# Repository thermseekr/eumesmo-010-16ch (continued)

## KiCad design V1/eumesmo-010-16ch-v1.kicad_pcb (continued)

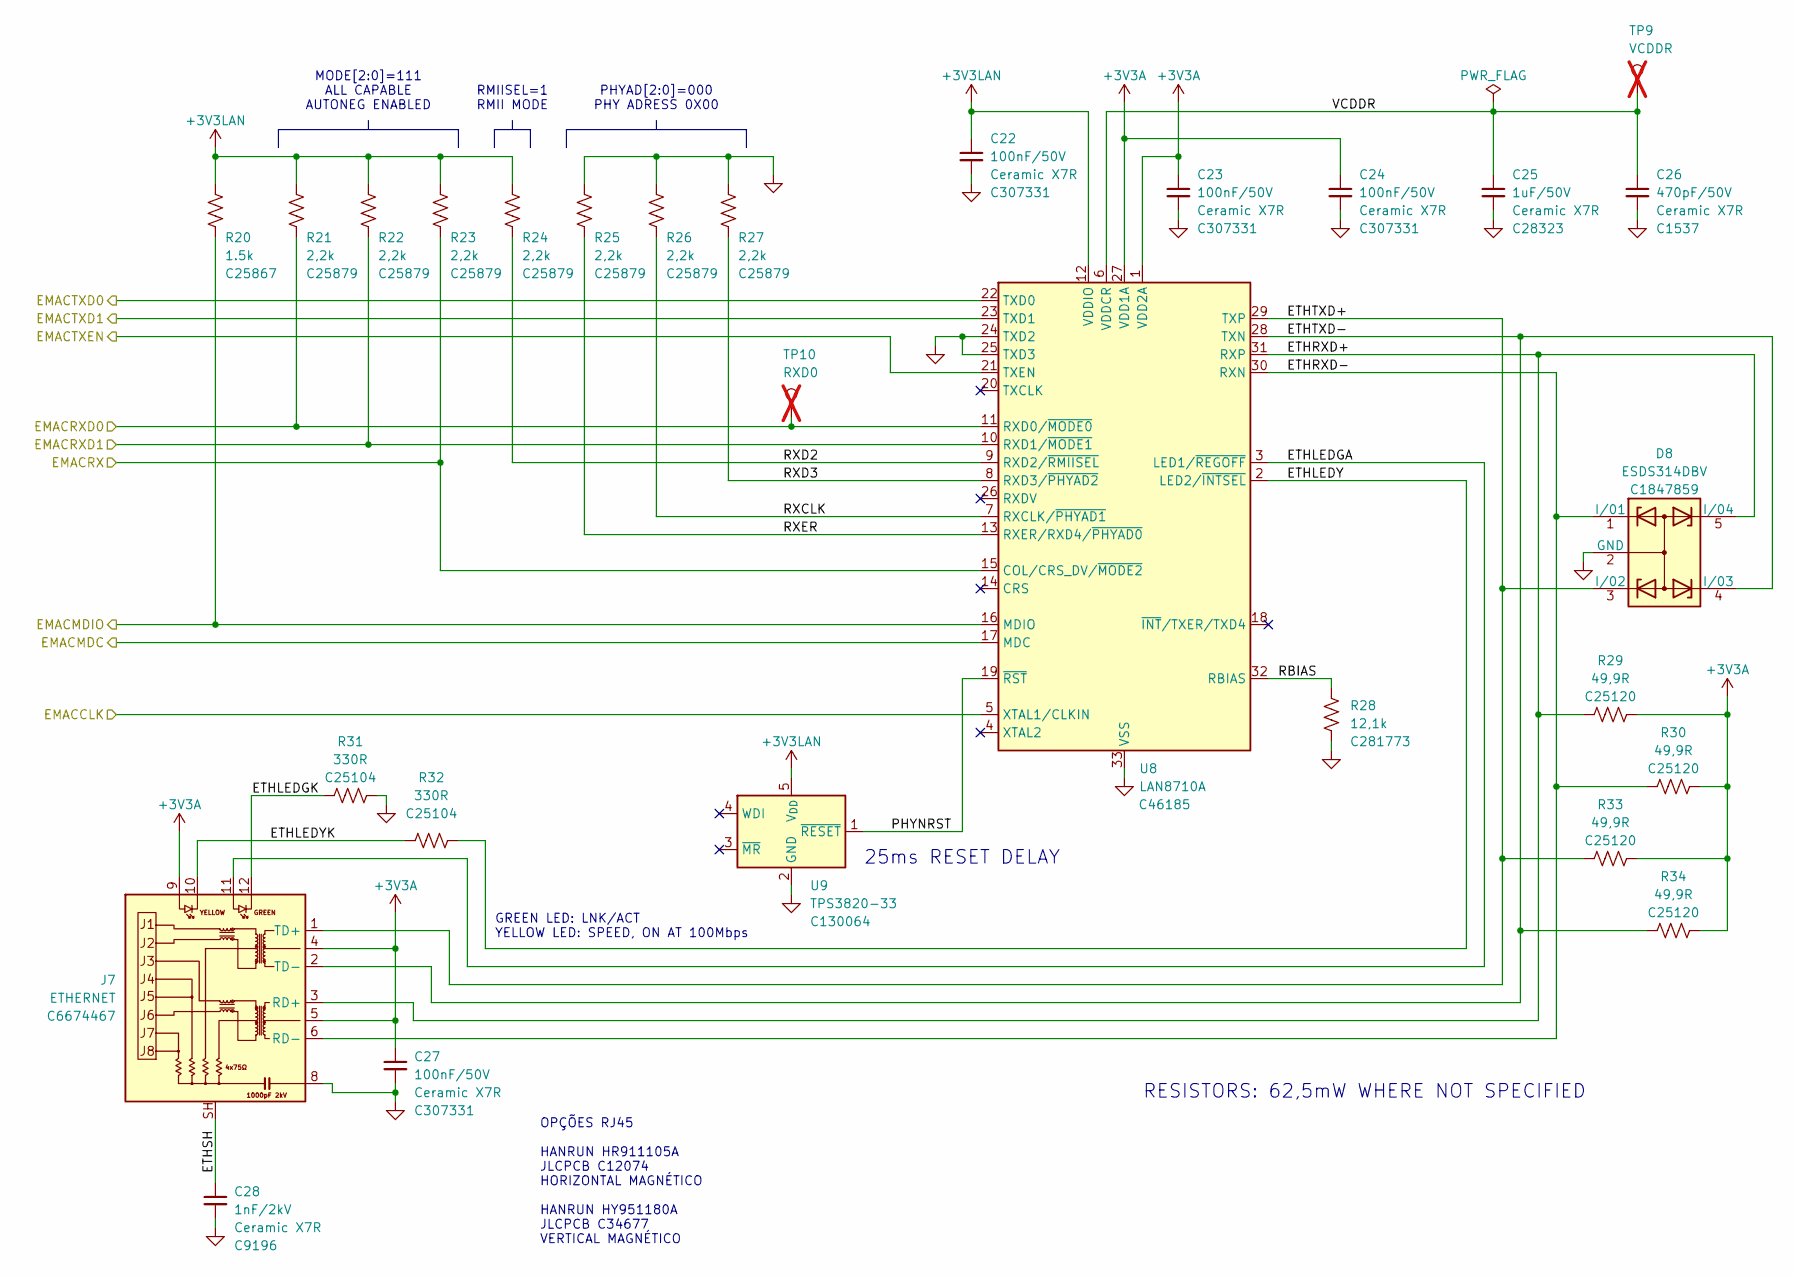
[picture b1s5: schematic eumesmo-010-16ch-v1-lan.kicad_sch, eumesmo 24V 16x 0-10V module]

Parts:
C22, C23, C24, C27: 100nF/50V; C_0402_1005Metric; Mfr PN CL05B104KB54PNC; LCSC Part # C307331
C25: 1uF/50V; C_0805_2012Metric; Mfr PN CL21B105KBFNNNE; LCSC Part # C28323
C26: 470pF/50V; C_0402_1005Metric; Mfr PN 0402B471K500NT; LCSC Part # C1537
C28: 1nF/2kV; C_1206_3216Metric; Mfr PN 1206B102K202NT; LCSC Part # C9196
D8: ESDS314DBV; SOT-23-5; Mfr PN ESDS314DBVR; LCSC Part # C1847859
J7: ETHERNET; RJ45_HanRun_HR915340A; Mfr PN HR915340AE; LCSC Part # C6674467
R20: 1.5k; R_0402_1005Metric; Mfr PN 0402WGF1501TCE; LCSC Part # C25867
R21, R22, R23, R24, R25, R26, R27: 2,2k; R_0402_1005Metric; Mfr PN 0402WGF2201TCE; LCSC Part # C25879
R28: 12,1k; R_0402_1005Metric; Mfr PN RT0402BRD0712K1L; LCSC Part # C281773
R29, R30, R33, R34: 49,9R; R_0402_1005Metric; Mfr PN 0402WGF499JTCE; LCSC Part # C25120
R31, R32: 330R; R_0402_1005Metric; Mfr PN 0402WGF3300TCE; LCSC Part # C25104
TP9: VCDDR; TestPoint_Pad_D1.5mm; not fitted
TP10: RXD0; TestPoint_Pad_D1.5mm; not fitted
U8: LAN8710A; QFN-32-1EP_5x5mm_P0.5mm_EP3.3x3.3mm_ThermalVias; Mfr PN LAN8710A-EZC-TR; LCSC Part # C46185
U9: TPS3820-33; SOT-23-5; Mfr PN TPS3820-33DBVR; LCSC Part # C130064

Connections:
+3V3A: C23.1, C24.1, C27.1, J7.4, J7.5, J7.9, R29.2, R30.2, R33.2, R34.2, U8.1 (VDD2A), U8.27 (VDD1A); also elsewhere on the board
+3V3LAN: C22.1, R20.1, R21.1, R22.1, R23.1, R24.1, U8.12 (VDDIO), U9.5 (V_{DD}); also elsewhere on the board
/LAN/EMACCLK: U8.5 (XTAL1/CLKIN); also elsewhere on the board
/LAN/EMACMDC: U8.17 (MDC); also elsewhere on the board
/LAN/EMACMDIO: R20.2, U8.16 (MDIO); also elsewhere on the board
/LAN/EMACRX: R23.2, U8.15 (COL/CRS_DV/~MODE2); also elsewhere on the board
/LAN/EMACRXD0: R21.2, TP10.1, U8.11 (RXD0/~MODE0); also elsewhere on the board
/LAN/EMACRXD1: R22.2, U8.10 (RXD1/~MODE1); also elsewhere on the board
/LAN/EMACTXD0: U8.22 (TXD0); also elsewhere on the board
/LAN/EMACTXD1: U8.23 (TXD1); also elsewhere on the board
/LAN/EMACTXEN: U8.21 (TXEN); also elsewhere on the board
/LAN/ETHLEDGA: J7.11, U8.3 (LED1/~REGOFF)
/LAN/ETHLEDGK: J7.12, R31.1
/LAN/ETHLEDY: R32.2, U8.2 (LED2/~INTSEL)
/LAN/ETHLEDYK: J7.10, R32.1
/LAN/ETHRXD+: D8.5 (I/04), J7.3 (RD+), R29.1, U8.31 (RXP)
/LAN/ETHRXD-: D8.1 (I/01), J7.6 (RD-), R30.1, U8.30 (RXN)
/LAN/ETHSH: C28.1, J7.SH
/LAN/ETHTXD+: D8.3 (I/02), J7.1 (TD+), R33.1, U8.29 (TXP)
/LAN/ETHTXD-: D8.4 (I/03), J7.2 (TD-), R34.1, U8.28 (TXN)
/LAN/PHYNRST: U8.19 (~RST), U9.1 (~RESET)
/LAN/RBIAS: R28.1, U8.32 (RBIAS)
/LAN/RXCLK: R26.2, U8.7 (RXCLK/~PHYAD1)
/LAN/RXD2: R24.2, U8.9 (RXD2/~RMIISEL)
/LAN/RXD3: R27.2, U8.8 (RXD3/~PHYAD2)
/LAN/RXER: R25.2, U8.13 (RXER/RXD4/~PHYAD0)
/LAN/VCDDR: C25.1, C26.1, U8.6 (VDDCR)
GND: C22.2, C23.2, C24.2, C25.2, C26.2, C27.2, C28.2, D8.2 (GND), J7.8, R25.1, R26.1, R27.1, R28.2, R31.2, U8.24 (TXD2), U8.25 (TXD3), U8.33 (VSS), U9.2 (GND); also elsewhere on the board

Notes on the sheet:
25ms RESET DELAY
OPÇÕES RJ45 HANRUN HR911105A JLCPCB C12074 HORIZONTAL MAGNÉTICO HANRUN HY951180A JLCPCB C34677 VERTICAL MAGNÉTICO
GREEN LED: LNK/ACT YELLOW LED: SPEED, ON AT 100Mbps
MODE[2:0]=111 ALL CAPABLE AUTONEG ENABLED
PHYAD[2:0]=000 PHY ADRESS 0X00
RMIISEL=1 RMII MODE
RESISTORS: 62,5mW WHERE NOT SPECIFIED

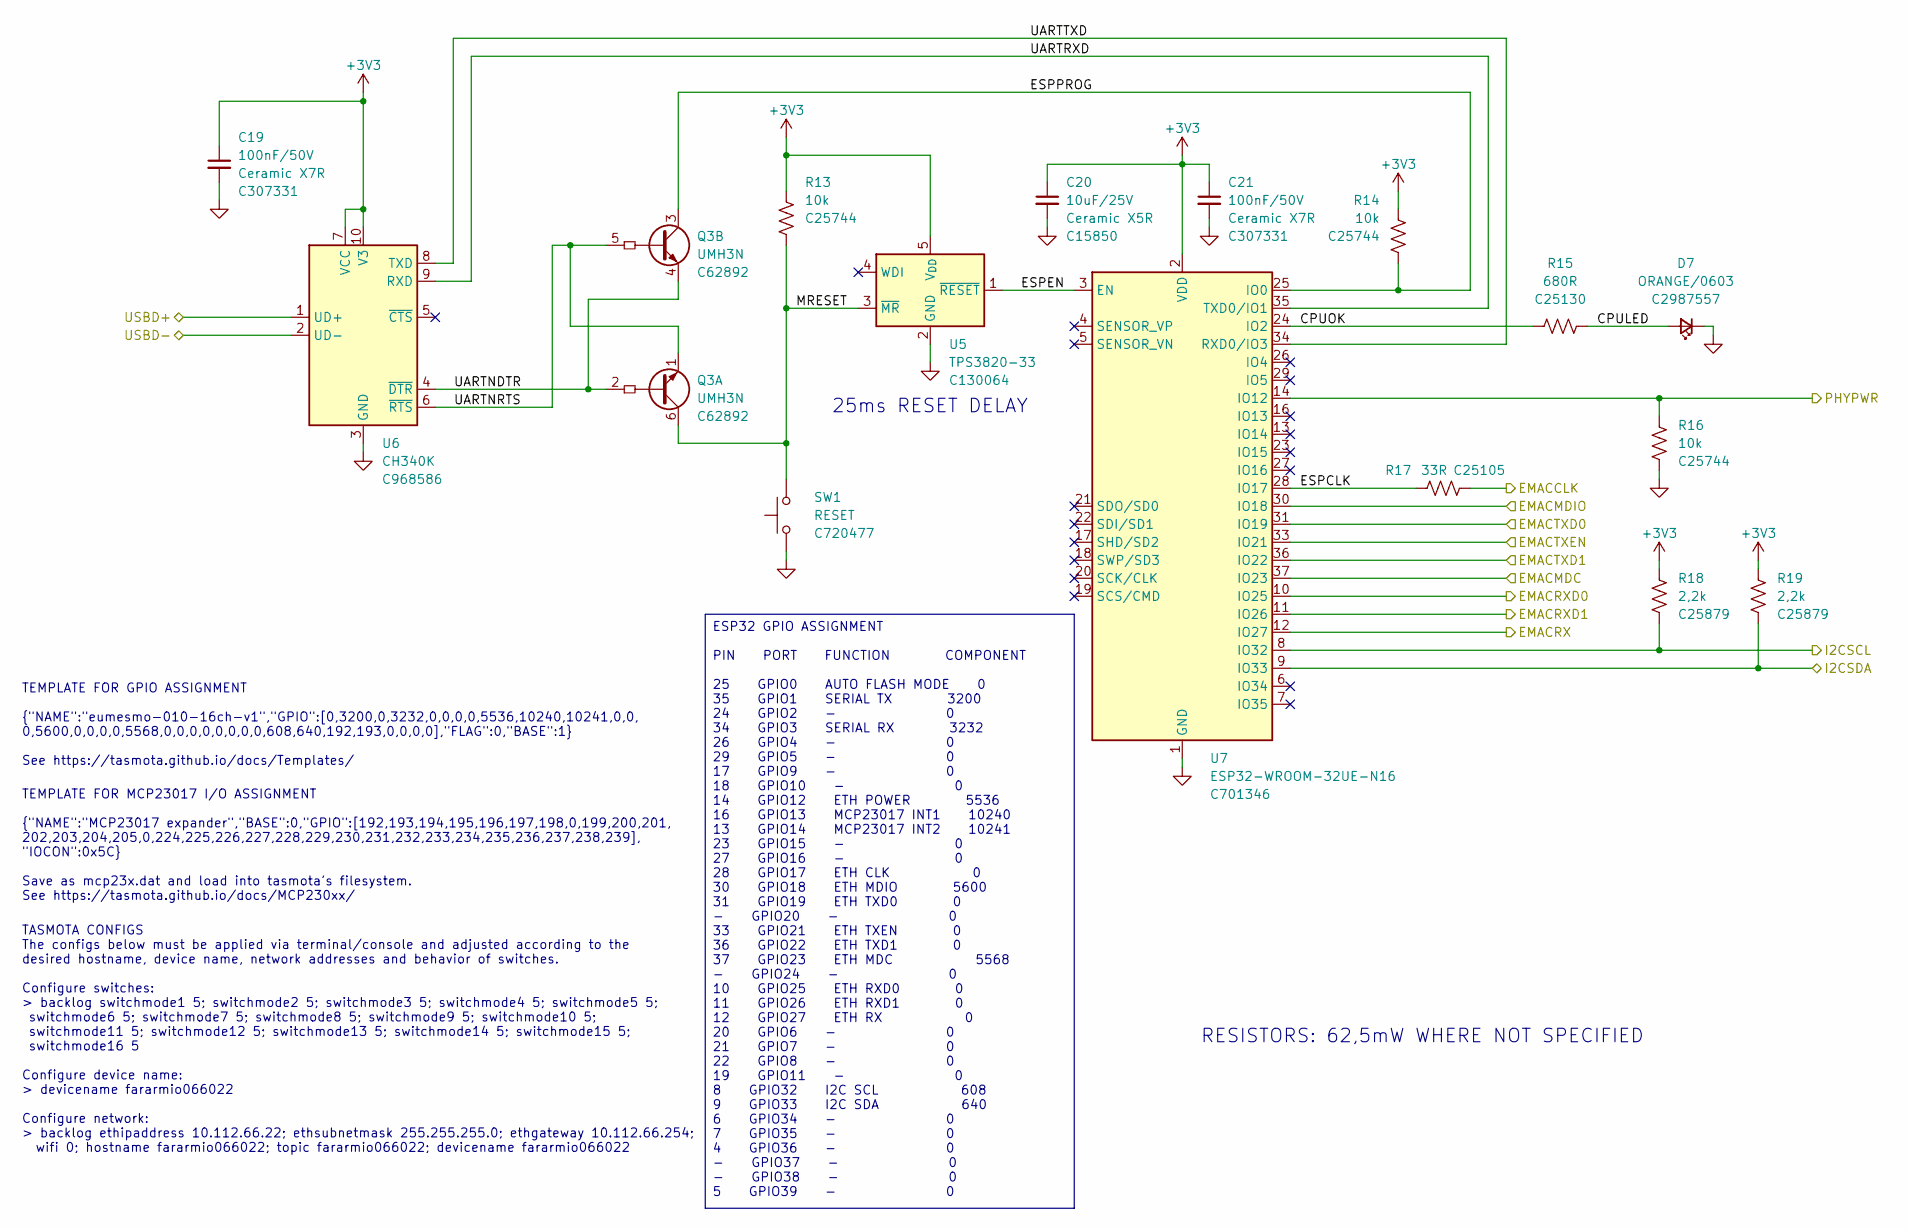
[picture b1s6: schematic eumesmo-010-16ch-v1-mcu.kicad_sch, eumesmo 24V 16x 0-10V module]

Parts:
C19, C21: 100nF/50V; C_0402_1005Metric; Mfr PN CL05B104KB54PNC; LCSC Part # C307331
C20: 10uF/25V; C_0805_2012Metric; Mfr PN CL21A106KAYNNNE; LCSC Part # C15850
D7: ORANGE/0603; LED_0603_1608Metric; Mfr PN 19-217/S2C-AL1M2VY/6T; LCSC Part # C2987557
Q3: UMH3N; SOT-363_SC-70-6; Mfr PN UMH3N; LCSC Part # C62892
R13, R14, R16: 10k; R_0402_1005Metric; Mfr PN 0402WGF1002TCE; LCSC Part # C25744
R15: 680R; R_0402_1005Metric; Mfr PN 0402WGF6800TCE; LCSC Part # C25130
R17: 33R; R_0402_1005Metric; Mfr PN 0402WGF330JTCE; LCSC Part # C25105
R18, R19: 2,2k; R_0402_1005Metric; Mfr PN 0402WGF2201TCE; LCSC Part # C25879
SW1: RESET; SW_SPST_Xunpu_TS1088AR02016; Mfr PN TS-1088-AR02016; LCSC Part # C720477
U5: TPS3820-33; SOT-23-5; Mfr PN TPS3820-33DBVR; LCSC Part # C130064
U6: CH340K; SSOP-10-1EP_3.9x4.9mm_P1mm_EP2.1x3.3mm; Mfr PN CH340K; LCSC Part # C968586
U7: ESP32-WROOM-32UE-N16; ESP32-WROOM-32U; Mfr PN ESP32-WROOM-32UE-N16; LCSC Part # C701346

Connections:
+3V3: C19.1, C20.1, C21.1, R13.1, R14.1, R18.1, R19.1, U5.5 (V_{DD}), U6.7 (VCC), U6.10 (V3), U7.2 (VDD); also elsewhere on the board
/I2C Devices/I2CSCL: R18.2, U7.8 (IO32); also elsewhere on the board
/I2C Devices/I2CSDA: R19.2, U7.9 (IO33); also elsewhere on the board
/LAN/EMACCLK: R17.2; also elsewhere on the board
/LAN/EMACMDC: U7.37 (IO23); also elsewhere on the board
/LAN/EMACMDIO: U7.30 (IO18); also elsewhere on the board
/LAN/EMACRX: U7.12 (IO27); also elsewhere on the board
/LAN/EMACRXD0: U7.10 (IO25); also elsewhere on the board
/LAN/EMACRXD1: U7.11 (IO26); also elsewhere on the board
/LAN/EMACTXD0: U7.31 (IO19); also elsewhere on the board
/LAN/EMACTXD1: U7.36 (IO22); also elsewhere on the board
/LAN/EMACTXEN: U7.33 (IO21); also elsewhere on the board
/MCU/CPULED: D7.2 (A), R15.2
/MCU/CPUOK: R15.1, U7.24 (IO2)
/MCU/ESPCLK: R17.1, U7.28 (IO17)
/MCU/ESPEN: U5.1 (~RESET), U7.3 (EN)
/MCU/ESPPROG: Q3.3 (C2), R14.2, U7.25 (IO0)
/MCU/MRESET: Q3.6 (C1), R13.2, SW1.2, U5.3 (~MR)
/MCU/PHYPWR: R16.1, U7.14 (IO12); also elsewhere on the board
/MCU/UARTNDTR: Q3.2 (B1), Q3.4 (E2), U6.4 (~DTR)
/MCU/UARTNRTS: Q3.1 (E1), Q3.5 (B2), U6.6 (~RTS)
/MCU/UARTRXD: U6.9 (RXD), U7.35 (TXD0/IO1)
/MCU/UARTTXD: U6.8 (TXD), U7.34 (RXD0/IO3)
/MCU/USBD+: U6.1 (UD+); also elsewhere on the board
/MCU/USBD-: U6.2 (UD-); also elsewhere on the board
GND: C19.2, C20.2, C21.2, D7.1 (K), R16.2, SW1.1, U5.2 (GND), U6.3 (GND), U6.11 (GND), U7.1 (GND), U7.15 (GND), U7.38 (GND), U7.39 (GND); also elsewhere on the board

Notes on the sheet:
TASMOTA CONFIGS The configs below must be applied via terminal/console and adjusted according to the desired hostname, device name, network addresses and behavior of switches. Configure switches: > backlog switchmode1 5; switchmode2 5; switchmode3 5; switchmode4 5; switchmode5 5; switchmode6 5; swi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
25ms RESET DELAY
TEMPLATE FOR GPIO ASSIGNMENT {"NAME":"eumesmo-010-16ch-v1","GPIO":[0,3200,0,3232,0,0,0,0,5536,10240,10241,0,0, 0,5600,0,0,0,0,5568,0,0,0,0,0,0,0,0,608,640,192,193,0,0,0,0],"FLAG":0,"BASE":1} See https://tasmota.github.io/docs/Templates/
TEMPLATE FOR MCP23017 I/O ASSIGNMENT {"NAME":"MCP23017 expander","BASE":0,"GPIO":[192,193,194,195,196,197,198,0,199,200,201, 202,203,204,205,0,224,225,226,227,228,229,230,231,232,233,234,235,236,237,238,239], "IOCON":0x5C} Save as mcp23x.dat and load into tasmota's filesystem. See https://tasmota.g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
RESISTORS: 62,5mW WHERE NOT SPECIFIED
ESP32 GPIO ASSIGNMENT PIN PORT FUNCTION COMPONENT 25 GPIO0 AUTO FLASH MODE 0 35 GPIO1 SERIAL TX 3200 24 GPIO2 - 0 34 GPIO3 SERIAL RX 3232 26 GPIO4 - 0 29 GPIO5 - 0 17 GPIO9 - 0 18 GPIO10 - 0 14 GPIO12 ETH POWER 5536 16 GPIO13 MCP23017 INT1 10240 13 GPIO14 MCP23017 INT2 10241 23 GPIO15 - 0 27 GPIO16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

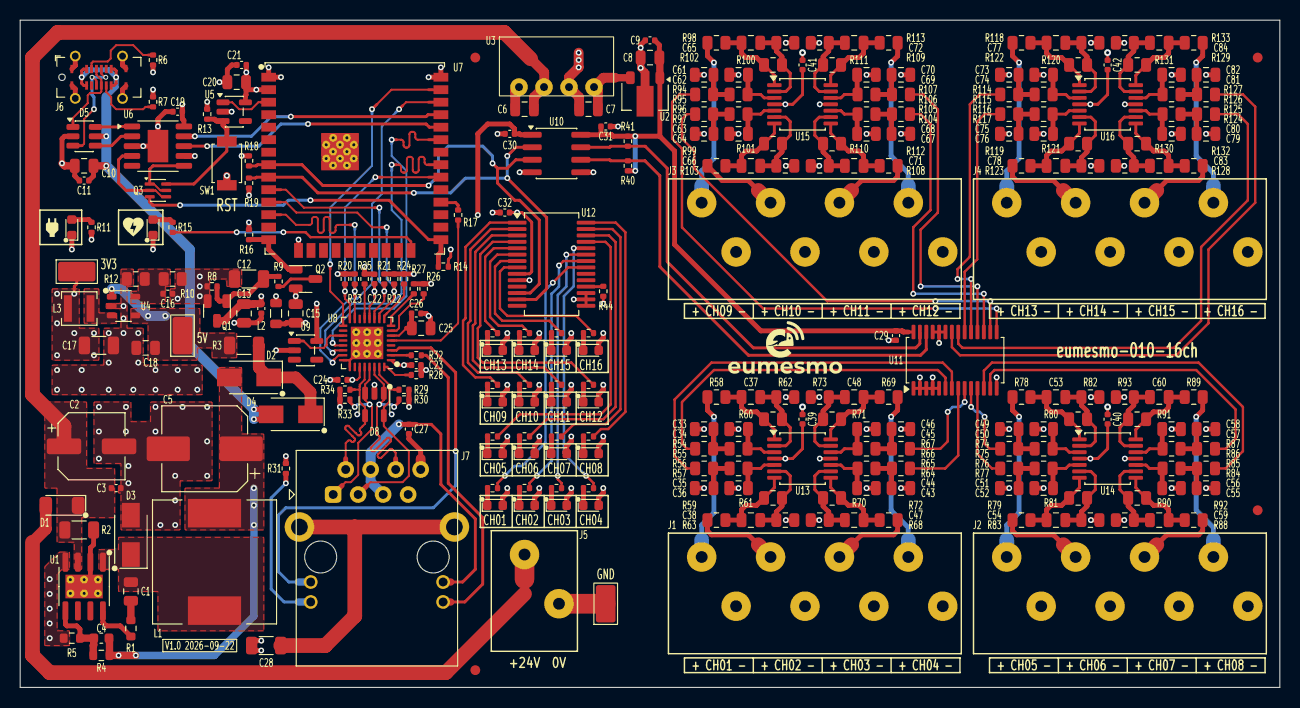
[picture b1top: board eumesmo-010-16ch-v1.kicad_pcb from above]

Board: 4 copper layers, 128.0 x 67.8 mm, 278 parts (0 on the bottom side), 198 nets.

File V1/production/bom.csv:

Designator,Footprint,Quantity,Value,LCSC Part #
"C1, C33, C34, C35, C36, C43, C44, C45, C46, C49, C50, C51, C52, C55, C56, C57, C58, C61, C62, C63, C64, C67, C68, C69, C70, C73, C74, C75, C76, C79, C80, C81, C82",0805,33,100nF/100V,C28233
"C10, C13, C15, C18, C20, C7",0805,6,10uF/25V,C15850
"C11, C14, C19, C21, C22, C23, C24, C27, C29, C3, C30, C31, C32, C39, C40, C41, C42, C9",0402,18,100nF/50V,C307331
"C12, C17",1206,2,22uF/10V,C5672
C16,0402,1,22pF/50V,C1555
C2,CP_Elec_6.3x5.4,1,47uF/35V,C129415
"C25, C6, C8",0805,3,1uF/50V,C28323
C26,0402,1,470pF/50V,C1537
C28,1206,1,1nF/2kV,C9196
"C37, C38, C47, C48, C53, C54, C59, C60, C65, C66, C71, C72, C77, C78, C83, C84",0805,16,100pF/50V,C1790
C4,0603,1,12pF/50V,C38523
C5,CP_Elec_8x10.5,1,470uF/16V,C96179
D1,D_SOD-123,1,SM4007PL,C64898
"D10, D11, D12, D13, D14, D15, D16, D17, D18, D19, D20, D21, D22, D23, D24, D6, D7, D9",0603,18,ORANGE/0603,C2987557
"D2, D4",D_SMA,2,SS34,C8678
D3,D_SMA,1,SS510,C65010
D5,SOT-23-6,1,USBLC6-2SC6,C7519
D8,SOT-23-5,1,ESDS314DBV,C1847859
"J1, J2, J3, J4",TerminalBlock_Wago_250-208_1x08_P3.5mm_45Degree,4,250-208,C2833587
J5,TerminalBlock_Wago_250-202_1x02_P3.5mm_45Degree,1,250-202,C2765061
J6,USB_C_Receptacle_ShouHan_TYPE-C-16PLT-H10.0,1,USB_C_Receptacle_USB2.0,C3151749
J7,RJ45_HanRun_HR915340A,1,ETHERNET,C6674467
L1,L_12x12mm_H6mm,1,"33uH 2,1A",C169386
L2,0805,1,2A 600R,C139168
L3,L_3x3mm_H1.5mm,1,"2,2uH 1,5A",C370424
Q1,SOT-23,1,WPM2015-3/TR,C558305
Q2,SOT-23,1,MMUN2211LT3G,C150229
Q3,SOT-363_SC-70-6,1,UMH3N,C62892
R1,0603,1,"5,1R/100mW",C25197
R10,0805,1,100k/125mW,C149504
"R100, R101, R110, R111, R120, R121, R130, R131, R60, R61, R70, R71, R80, R81, R90, R91",0805,16,11k/125mW,C17429
"R102, R103, R104, R105, R106, R107, R112, R113, R114, R115, R116, R117, R122, R123, R124, R125, R126, R127, R132, R133, R54, R55, R56, R57, R62, R63, R64, R65, R66, R67, R72, R73, R74, R75, R76, R77, R82, R83, R84, R85, R86, R87, R92, R93, R94, R95, R96, R97",0805,48,10k/125mW,C17414
"R108, R109, R118, R119, R128, R129, R58, R59, R68, R69, R78, R79, R88, R89, R98, R99",0805,16,47R/125mW,C17714
"R11, R15, R35, R36, R37, R38, R39, R42, R43, R45, R46, R47, R48, R49, R50, R51, R52, R53",0402,18,680R,C25130
R12,0805,1,"22,1k/125mW",C17552
"R13, R14, R16, R8",0402,4,10k,C25744
R17,0402,1,33R,C25105
"R18, R19, R21, R22, R23, R24, R25, R26, R27, R40, R41",0402,11,"2,2k",C25879
R2,1206,1,30mR/333mW,C473665
R20,0402,1,1.5k,C25867
R28,0402,1,"12,1k",C281773
"R29, R30, R33, R34",0402,4,"49,9R",C25120
R3,1206,1,"0,1R",C309528
"R31, R32",0402,2,330R,C25104
R4,0603,1,300k/100mW,C23024
"R44, R9",0402,2,1k,C11702
R5,0603,1,"52,3k/100mW",C23198
"R6, R7",0402,2,"5,1k",C105872
SW1,SW_SPST_Xunpu_TS1088AR02016,1,RESET,C720477
"TP2, TP3, TP8",TestPoint_Keystone_5019_Miniature,3,TP5019,C238131
U1,SOIC-8-1EP_3.9x4.9mm_P1.27mm_EP2.41x3.81mm_ThermalVias,1,TX4138,C329267
U10,SOIC-8_3.9x4.9mm_P1.27mm,1,ISO1540,C179739
U11,TSSOP-28_4.4x9.7mm_P0.65mm,1,PCA9685PW,C2678753
U12,SSOP-28_5.3x10.2mm_P0.65mm,1,MCP23017,C506653
"U13, U14, U15, U16",TSSOP-14_4.4x5mm_P0.65mm,4,TLV274,C9914
U2,SOT-89-3,1,L78L05_SOT89,C42738
U3,Ylptec BxxxxS-1WR3,1,B2412S-1WR3,C5369469
U4,SOT-23-5_Shorter_Pins,1,SY8089A1AAC,C479074
"U5, U9",SOT-23-5,2,TPS3820-33,C130064
U6,SSOP-10-1EP_3.9x4.9mm_P1mm_EP2.1x3.3mm,1,CH340K,C968586
U7,ESP32-WROOM-32U,1,ESP32-WROOM-32UE-N16,C701346
U8,QFN-32-1EP_5x5mm_P0.5mm_EP3.3x3.3mm_ThermalVias,1,LAN8710A,C46185

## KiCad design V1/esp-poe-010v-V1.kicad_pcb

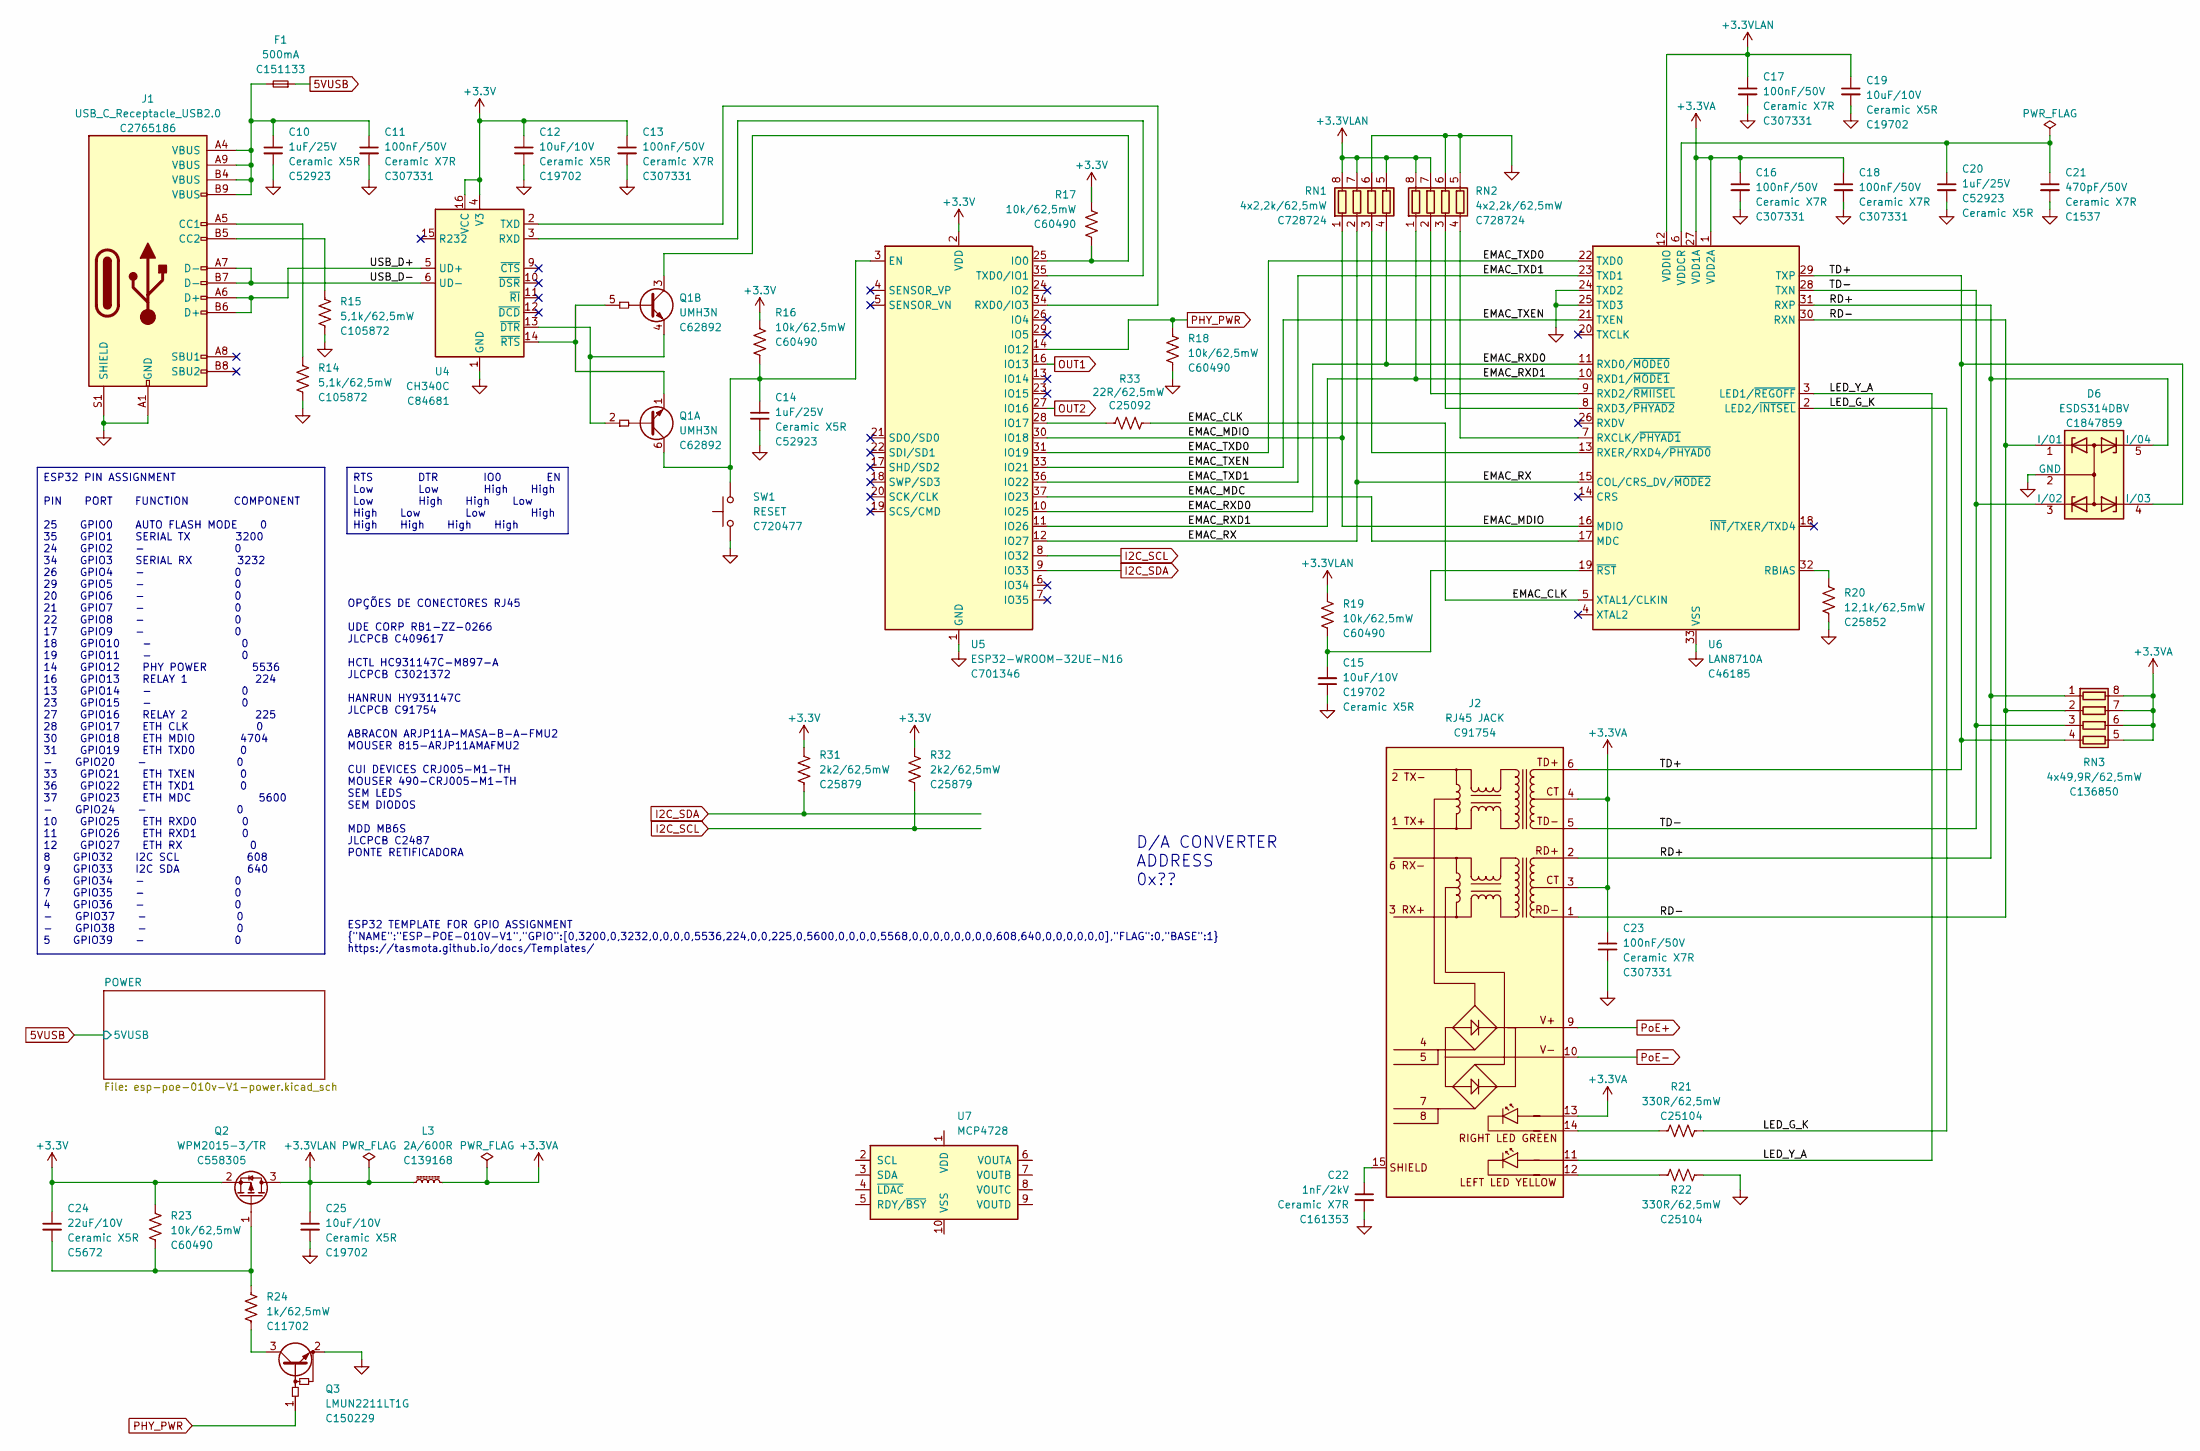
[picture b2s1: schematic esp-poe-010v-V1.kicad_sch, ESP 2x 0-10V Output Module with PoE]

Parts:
C10, C14, C20: 1uF/25V; C_0402_1005Metric; Mfr PN CL05A105KA5NQNC; JLCPCB BOM 1
C11, C13, C16, C17, C18, C23: 100nF/50V; C_0402_1005Metric; Mfr PN CL05B104KB54PNC; JLCPCB BOM 1
C12: 10uF/10V; C_0603_1608Metric; Mfr PN CL10A106KP8NNNC; LCSC Part # C19702
C15, C19, C25: 10uF/10V; C_0603_1608Metric; Mfr PN CL10A106KP8NNNC; JLCPCB BOM 1
C21: 470pF/50V; C_0402_1005Metric; Mfr PN 0402B471K500NT; JLCPCB BOM 1
C22: 1nF/2kV; C_1206_3216Metric; Mfr PN GR431BR7LA102KW66L; JLCPCB BOM 1
C24: 22uF/10V; C_1206_3216Metric; Mfr PN CL31A226KPHNNNE; JLCPCB BOM 1
D6: ESDS314DBV; SOT-23-5; Mfr PN ESDS314DBVR; JLCPCB BOM 1
F1: 500mA; Fuse_1206_3216Metric; Mfr PN 0466.500NRHF; JLCPCB BOM 1
J1: USB_C_Receptacle_USB2.0; USB_C_Receptacle_GCT_USB4105-xx-A_16P_TopMnt_Horizontal; Mfr PN TYPE-C 16PIN 2MD(073); JLCPCB BOM 1
J2: RJ45 JACK; RJ45_HanRun_HY931147C; Mfr PN HY931147C; JLCPCB BOM 1
L3: 2A/600R; L_0805_2012Metric; Mfr PN CBM201209U601T; JLCPCB BOM 1
Q1: UMH3N; SOT-363_SC-70-6; Mfr PN UMH3N; JLCPCB BOM 1
Q2: WPM2015-3/TR; SOT-23; Mfr PN WPM2015-3/TR; JLCPCB BOM 1
Q3: LMUN2211LT1G; SOT-23; Mfr PN MMUN2211LT3G; LCSC Part # C150229
R14, R15: 5,1k/62,5mW; R_0402_1005Metric; Mfr PN RC0402FR-075K1L; JLCPCB BOM 1
R16, R17, R18, R19, R23: 10k/62,5mW; R_0402_1005Metric; Mfr PN RC0402FR-0710KL; LCSC Part # C60490
R20: 12,1k/62,5mW; R_0402_1005Metric; Mfr PN 0402WGF1212TCE; JLCPCB BOM 1
R21, R22: 330R/62,5mW; R_0402_1005Metric; Mfr PN 0402WGF3300TCE; LCSC Part # C25104
R24: 1k/62,5mW; R_0402_1005Metric; Mfr PN 0402WGF1001TCE; LCSC Part # C11702
R31, R32: 2k2/62,5mW; R_0402_1005Metric; Mfr PN 0402WGF2201TCE; LCSC Part # C25879
R33: 22R/62,5mW; R_0402_1005Metric; Mfr PN 0402WGF220JTCE; JLCPCB BOM 1
RN1, RN2: 4x2,2k/62,5mW; R_Array_Convex_4x0402; Mfr PN YC124-FR-072K2L; JLCPCB BOM 1
RN3: 4x49,9R/62,5mW; R_Array_Convex_4x0402; Mfr PN YC124-FR-0749R9L; JLCPCB BOM 1
SW1: RESET; SW_SPST_Xunpu_TS1088AR02016; Mfr PN TS-1088-AR02016; JLCPCB BOM 1
U4: CH340C; SOIC-16_3.9x9.9mm_P1.27mm; Mfr PN CH340C; JLCPCB BOM 1
U5: ESP32-WROOM-32UE-N16; ESP32-WROOM-32U; Mfr PN ESP32-WROOM-32UE-N16; JLCPCB BOM 1
U6: LAN8710A; QFN-32-1EP_5x5mm_P0.5mm_EP3.3x3.3mm_ThermalVias; Mfr PN LAN8710A-EZC-TR; JLCPCB BOM 1
U7: MCP4728; MSOP-10_3x3mm_P0.5mm

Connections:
5VUSB: F1.1; also elsewhere on the board
+3.3V: C12.1, C13.1, C24.1, Q2.2 (S), R16.1, R17.1, R23.1, R31.1, R32.1, U4.4 (V3), U4.16 (VCC), U5.2 (VDD); also elsewhere on the board
+3.3VA: C16.1, C18.1, C23.1, J2.3 (CT), J2.4 (CT), J2.13 (RLED+), L3.2, RN3.5 (R4.2), RN3.6 (R3.2), RN3.7 (R2.2), RN3.8 (R1.2), U6.1 (VDD2A), U6.27 (VDD1A)
+3.3VLAN: C17.1, C19.1, C25.1, L3.1, Q2.3 (D), R19.2, RN1.5 (R4.2), RN1.7 (R2.2), RN1.8 (R1.2), RN2.7 (R2.2), RN2.8 (R1.2), U6.12 (VDDIO)
/EMAC_CLK: R33.2, U6.5 (XTAL1/CLKIN)
/EMAC_MDC: U5.37 (IO23), U6.17 (MDC)
/EMAC_MDIO: RN1.1 (R1.1), U5.30 (IO18), U6.16 (MDIO)
/EMAC_RX: RN1.2 (R2.1), U5.12 (IO27), U6.15 (COL/CRS_DV/~MODE2)
/EMAC_RXD0: RN1.4 (R4.1), U5.10 (IO25), U6.11 (RXD0/~MODE0)
/EMAC_RXD1: RN2.1 (R1.1), U5.11 (IO26), U6.10 (RXD1/~MODE1)
/EMAC_TXD0: U5.31 (IO19), U6.22 (TXD0)
/EMAC_TXD1: U5.36 (IO22), U6.23 (TXD1)
/EMAC_TXEN: U5.33 (IO21), U6.21 (TXEN)
/LED_G_K: R21.2, U6.2 (LED2/~INTSEL)
/LED_Y_A: J2.11 (LLED+), U6.3 (LED1/~REGOFF)
/RD+: D6.5 (I/04), J2.2 (RD+), RN3.1 (R1.1), U6.31 (RXP)
/RD-: D6.1 (I/01), J2.1 (RD-), RN3.2 (R2.1), U6.30 (RXN)
/TD+: D6.4 (I/03), J2.6 (TD+), RN3.4 (R4.1), U6.29 (TXP)
/TD-: D6.3 (I/02), J2.5 (TD-), RN3.3 (R3.1), U6.28 (TXN)
/USB_D+: J1.A6 (D+), J1.B6 (D+), U4.5 (UD+)
/USB_D-: J1.A7 (D-), J1.B7 (D-), U4.6 (UD-)
GND: C10.2, C11.2, C12.2, C13.2, C14.2, C15.1, C16.2, C17.2, C18.2, C19.2, C20.2, C21.2, C22.2, C23.2, C25.2, D6.2 (GND), J1.A1 (GND), J1.A12 (GND), J1.B1 (GND), J1.B12 (GND), J1.S1 (SHIELD), Q3.2 (E), R14.2, R15.2, R18.1, R20.2, R22.2, RN1.6 (R3.2), RN2.5 (R4.2), RN2.6 (R3.2), SW1.1, U4.1 (GND), U5.1 (GND), U5.15 (GND), U5.38 (GND), U5.39 (GND), U6.24 (TXD2), U6.25 (TXD3), U6.33 (VSS); also elsewhere on the board
I2C_SCL: R32.2, U5.8 (IO32)
I2C_SDA: R31.2, U5.9 (IO33)
unnamed: C10.1, C11.1, F1.2, J1.A4 (VBUS), J1.A9 (VBUS), J1.B4 (VBUS), J1.B9 (VBUS)
unnamed: J1.A5 (CC1), R14.1
unnamed: J1.B5 (CC2), R15.1
unnamed: J2.12 (LLED-), R22.1
unnamed: J2.14 (RLED-), R21.1
unnamed: C22.1, J2.15 (SHIELD)
unnamed: Q1.2 (B1), Q1.4 (E2), U4.13 (~DTR)
unnamed: C14.1, Q1.6 (C1), R16.2, SW1.2, U5.3 (EN)
unnamed: Q1.1 (E1), Q1.5 (B2), U4.14 (~RTS)
unnamed: Q1.3 (C2), R17.2, U5.25 (IO0)
unnamed: C24.2, Q2.1 (G), R23.2, R24.1
unnamed: Q3.3 (C), R24.2
unnamed: RN1.3 (R3.1), U6.13 (RXER/RXD4/~PHYAD0)
unnamed: RN2.2 (R2.1), U6.9 (RXD2/~RMIISEL)
unnamed: RN2.3 (R3.1), U6.8 (RXD3/~PHYAD2)
unnamed: RN2.4 (R4.1), U6.7 (RXCLK/~PHYAD1)
unnamed: U4.3 (RXD), U5.35 (TXD0/IO1)
unnamed: U4.2 (TXD), U5.34 (RXD0/IO3)
unnamed: R33.1, U5.28 (IO17)
unnamed: R20.1, U6.32 (RBIAS)
unnamed: C20.1, C21.1, U6.6 (VDDCR)
unnamed: C15.2, R19.1, U6.19 (~RST)
OUT1: U5.16 (IO13)
OUT2: U5.27 (IO16)
PHY_PWR: Q3.1 (B), R18.2, U5.14 (IO12)
PoE+: J2.9 (V+); also elsewhere on the board
PoE-: J2.10 (V-); also elsewhere on the board

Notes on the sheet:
D/A CONVERTER ADDRESS 0x??
OPÇÕES DE CONECTORES RJ45 UDE CORP RB1-ZZ-0266 JLCPCB C409617 HCTL HC931147C-M897-A JLCPCB C3021372 HANRUN HY931147C JLCPCB C91754 ABRACON ARJP11A-MASA-B-A-FMU2 MOUSER 815-ARJP11AMAFMU2 CUI DEVICES CRJ005-M1-TH MOUSER 490-CRJ005-M1-TH SEM LEDS SEM DIODOS MDD MB6S JLCPCB C2487 PONTE RETIFICADORA
ESP32 TEMPLATE FOR GPIO ASSIGNMENT {"NAME":"ESP-POE-010V-V1","GPIO":[0,3200,0,3232,0,0,0,0,5536,224,0,0,225,0,5600,0,0,0,0,5568,0,0,0,0,0,0,0,0,608,640,0,0,0,0,0,0],"FLAG":0,"BASE":1} https://tasmota.github.io/docs/Templates/
ESP32 PIN ASSIGNMENT PIN PORT FUNCTION COMPONENT 25 GPIO0 AUTO FLASH MODE 0 35 GPIO1 SERIAL TX 3200 24 GPIO2 - 0 34 GPIO3 SERIAL RX 3232 26 GPIO4 - 0 29 GPIO5 - 0 20 GPIO6 - 0 21 GPIO7 - 0 22 GPIO8 - 0 17 GPIO9 - 0 18 GPIO10 - 0 19 GPIO11 - 0 14 GPIO12 PHY POWER 5536 16 GPIO13 RELAY 1 224 13 GPIO14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
RTS DTR IO0 EN Low Low High High Low High High Low High Low Low High High High High High

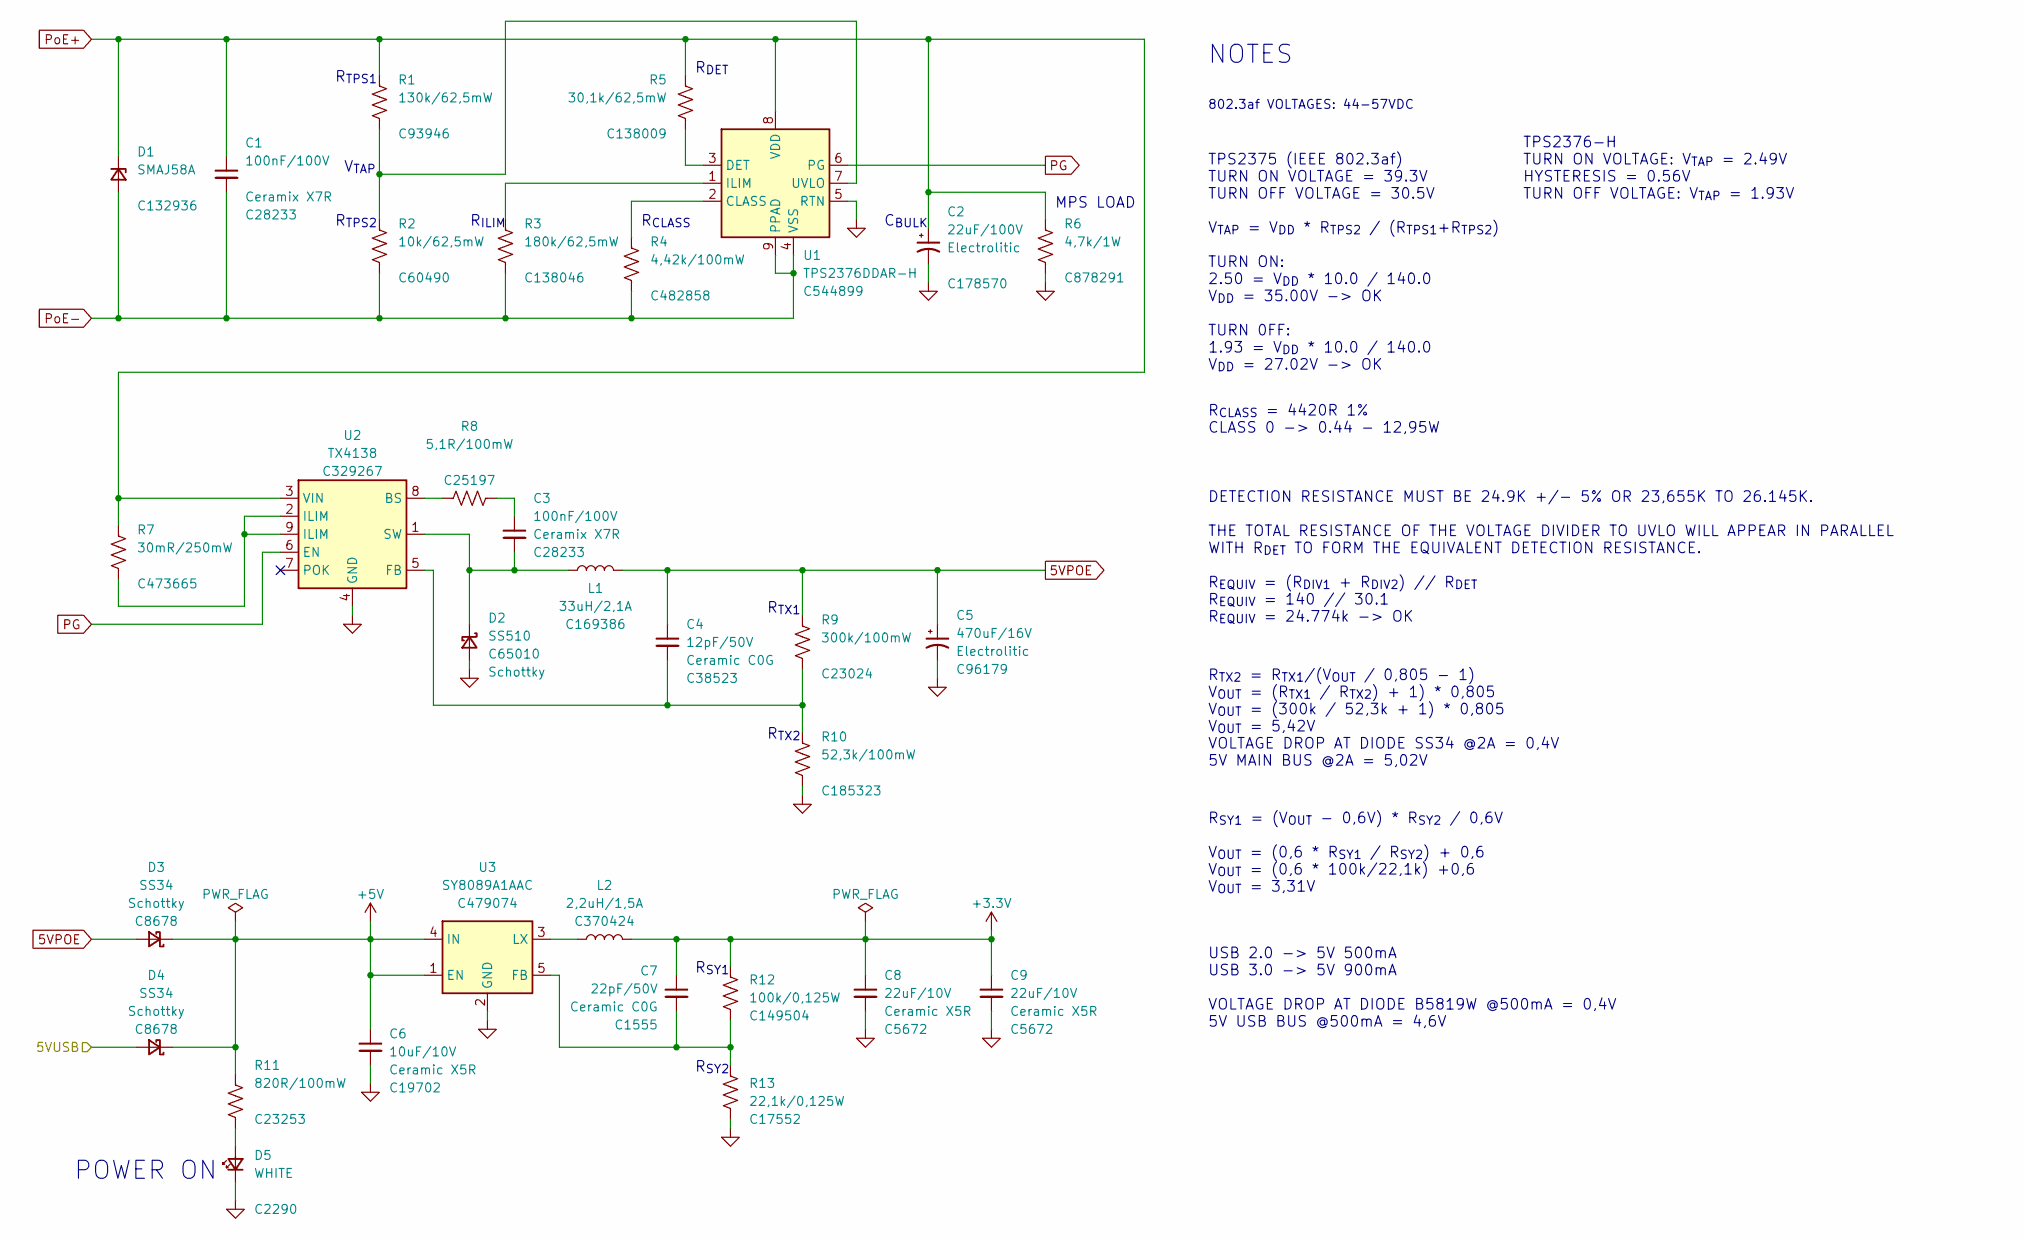
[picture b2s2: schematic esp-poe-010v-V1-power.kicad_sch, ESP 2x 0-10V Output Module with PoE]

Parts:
C1: 100nF/100V; C_0805_2012Metric; Mfr PN CL21B104KCFNNNE; JLCPCB BOM 1
C2: 22uF/100V; CP_Elec_8x10.5; Mfr PN EEEFK2A220P; LCSC Part # C178570
C3: 100nF/100V; C_0805_2012Metric; Mfr PN CL21B104KCFNNNE; LCSC Part # C28233
C4: 12pF/50V; C_0603_1608Metric; Mfr PN CL10C120JB8NNNC; JLCPCB BOM 1
C5: 470uF/16V; CP_Elec_8x10.5; Mfr PN CS1C471M-CRF10; JLCPCB BOM 1
C6: 10uF/10V; C_0603_1608Metric; Mfr PN CL10A106KP8NNNC; JLCPCB BOM 1
C7: 22pF/50V; C_0402_1005Metric; Mfr PN 0402CG220J500NT; JLCPCB BOM 1
C8, C9: 22uF/10V; C_1206_3216Metric; Mfr PN CL31A226KPHNNNE; JLCPCB BOM 1
D1: SMAJ58A; D_SMA; Mfr PN SMAJ58A-TR; JLCPCB BOM 1
D2: SS510; D_SMA; Mfr PN SS510; JLCPCB BOM 1
D3, D4: SS34; D_SMA; Mfr PN SS34; JLCPCB BOM 1
D5: WHITE; LED_0603_1608Metric; Mfr PN KT-0603W; LCSC Part # C2290
L1: 33uH/2,1A; L_12x12mm_h6mm; Mfr PN SWRB1205S-330MT; JLCPCB BOM 1
L2: 2,2uH/1,5A; L_3x3mm_h1.5mm; Mfr PN SPH3015H2R2MT; JLCPCB BOM 1
R1: 130k/62,5mW; R_0402_1005Metric; Mfr PN RC0402FR-07130KL; JLCPCB BOM 1
R2: 10k/62,5mW; R_0402_1005Metric; Mfr PN RC0402FR-0710KL; JLCPCB BOM 1
R3: 180k/62,5mW; R_0402_1005Metric; Mfr PN RC0402FR-07180KL; JLCPCB BOM 1
R4: 4,42k/100mW; R_0603_1608Metric; Mfr PN RC0603FR-074K42L; JLCPCB BOM 1
R5: 30,1k/62,5mW; R_0402_1005Metric; Mfr PN RC0402FR-0730K1L; JLCPCB BOM 1
R6: 4,7k/1W; R_2512_6332Metric; Mfr PN RC2512JK-074K7L; JLCPCB BOM 1
R7: 30mR/250mW; R_1206_3216Metric; Mfr PN 1206W3F300MT5E; LCSC Part # C473665
R8: 5,1R/100mW; R_0603_1608Metric; Mfr PN 0603WAF510KT5E; LCSC Part # C25197
R9: 300k/100mW; R_0603_1608Metric; Mfr PN 0603WAF3003T5E; JLCPCB BOM 1
R10: 52,3k/100mW; R_0603_1608Metric; Mfr PN RC0603FR-0752K3L; JLCPCB BOM 1
R11: 820R/100mW; R_0603_1608Metric; Mfr PN 0603WAF8200T5E; LCSC Part # C23253
R12: 100k/0,125W; R_0805_2012Metric; Mfr PN 0805W8F1003T5E; JLCPCB BOM 1
R13: 22,1k/0,125W; R_0805_2012Metric; Mfr PN 0805W8F2212T5E; JLCPCB BOM 1
U1: TPS2376DDAR-H; SOIC-8-1EP_3.9x4.9mm_P1.27mm_EP2.95x4.9mm_Mask2.71x3.4mm_Th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; Mfr PN TPS2376DDAR-H; JLCPCB BOM 1
U2: TX4138; SOIC-8-1EP_3.9x4.9mm_P1.27mm_EP2.41x3.81mm_ThermalVias; Mfr PN TX4138; JLCPCB BOM 1
U3: SY8089A1AAC; SOT-23-5_Shorter_Pins; Mfr PN SY8089A1AAC; JLCPCB BOM 1

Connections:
5VPOE: C4.1, C5.1, D3.2 (A), L1.2, R9.1
5VUSB: D4.2 (A); also elsewhere on the board
+3.3V: C7.1, C8.1, C9.1, L2.2, R12.1; also elsewhere on the board
+5V: C6.1, D3.1 (K), D4.1 (K), R11.1, U3.1 (EN), U3.4 (IN)
GND: C2.2, C5.2, C6.2, C8.2, C9.2, D2.2 (A), D5.1 (K), R6.2, R10.2, R13.2, U1.5 (RTN), U2.4 (GND), U3.2 (GND); also elsewhere on the board
unnamed: C3.1, R8.1
unnamed: C3.2, D2.1 (K), L1.1, U2.1 (SW)
unnamed: D5.2 (A), R11.2
unnamed: R7.2, U2.2 (ILIM), U2.9 (ILIM)
unnamed: R4.1, U1.2 (CLASS)
unnamed: R5.2, U1.3 (DET)
unnamed: R3.1, U1.1 (ILIM)
unnamed: R1.2, R2.1, U1.7 (UVLO)
unnamed: R8.2, U2.8 (BS)
unnamed: C4.2, R9.2, R10.1, U2.5 (FB)
unnamed: C7.2, R12.2, R13.1, U3.5 (FB)
unnamed: L2.1, U3.3 (LX)
PG: U1.6 (PG), U2.6 (EN)
PoE+: C1.1, C2.1, D1.1 (K), R1.1, R5.1, R6.1, R7.1, U1.8 (VDD), U2.3 (VIN); also elsewhere on the board
PoE-: C1.2, D1.2 (A), R2.2, R3.2, R4.2, U1.4 (VSS), U1.9 (PPAD); also elsewhere on the board

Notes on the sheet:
R_{TPS1}
R_{TX2}
DETECTION RESISTANCE MUST BE 24.9K +/- 5% OR 23,655K TO 26.145K. THE TOTAL RESISTANCE OF THE VOLTAGE DIVIDER TO UVLO WILL APPEAR IN PARALLEL WITH R_{DET} TO FORM THE EQUIVALENT DETECTION RESISTANCE. R_{EQUIV} = (R_{DIV1} + R_{DIV2}) // R_{DET} R_{EQUIV} = 140 // 30.1 R_{EQUIV} = 24.774k -> OK
R_{SY2}
POWER ON
R_{CLASS} = 4420R 1% CLASS 0 -> 0.44 - 12,95W
R_{SY1}
R_{CLASS}
R_{TX2} = R_{TX1}/(V_{OUT} / 0,805 - 1) V_{OUT} = (R_{TX1} / R_{TX2}) + 1) * 0,805 V_{OUT} = (300k / 52,3k + 1) * 0,805 V_{OUT} = 5,42V VOLTAGE DROP AT DIODE SS34 @2A = 0,4V 5V MAIN BUS @2A = 5,02V
C_{BULK}
R_{ILIM}
USB 2.0 -> 5V 500mA USB 3.0 -> 5V 900mA VOLTAGE DROP AT DIODE B5819W @500mA = 0,4V 5V USB BUS @500mA = 4,6V
TPS2375 (IEEE 802.3af) TURN ON VOLTAGE = 39.3V TURN OFF VOLTAGE = 30.5V
V_{TAP}
TPS2376-H TURN ON VOLTAGE: V_{TAP} = 2.49V HYSTERESIS = 0.56V TURN OFF VOLTAGE: V_{TAP} = 1.93V
R_{SY1} = (V_{OUT} - 0,6V) * R_{SY2} / 0,6V V_{OUT} = (0,6 * R_{SY1} / R_{SY2}) + 0,6 V_{OUT} = (0,6 * 100k/22,1k) +0,6 V_{OUT} = 3,31V
R_{TPS2}
R_{TX1}
NOTES
MPS LOAD
R_{DET}
802.3af VOLTAGES: 44-57VDC
V_{TAP} = V_{DD} * R_{TPS2} / (R_{TPS1}+R_{TPS2}) TURN ON: 2.50 = V_{DD} * 10.0 / 140.0 V_{DD} = 35.00V -> OK TURN 0FF: 1.93 = V_{DD} * 10.0 / 140.0 V_{DD} = 27.02V -> OK
